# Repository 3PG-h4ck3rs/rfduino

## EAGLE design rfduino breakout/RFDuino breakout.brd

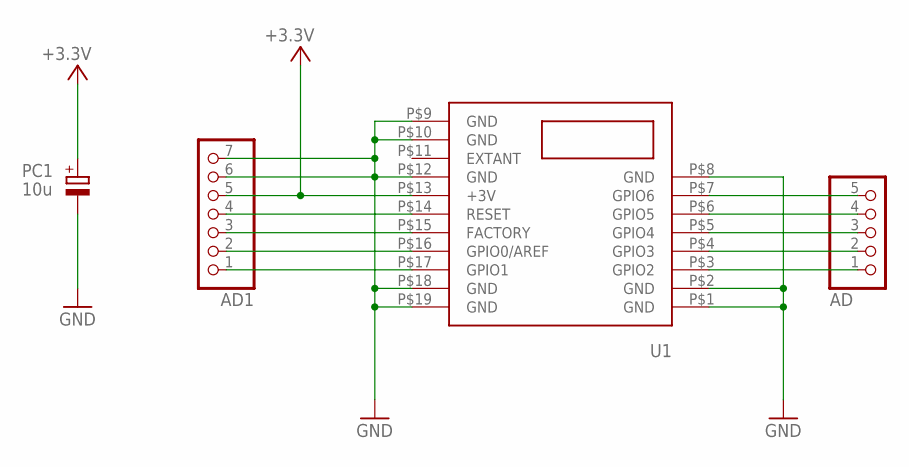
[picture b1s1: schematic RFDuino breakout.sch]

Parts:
AD: PINHD-1X5; 1X05
AD1: PINHD-1X7; 1X07
PC1: 10u; PANASONIC_D
U1: RFD22301

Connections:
3.3V: AD1.5, PC1.+, U1.P$13 (+3V)
FACTORY: AD1.3, U1.P$15 (FACTORY)
GND: AD1.6, AD1.7, PC1.-, U1.P$1 (GND), U1.P$2 (GND), U1.P$8 (GND), U1.P$9 (GND), U1.P$10 (GND), U1.P$12 (GND), U1.P$18 (GND), U1.P$19 (GND)
GPIO0: AD1.2, U1.P$16 (GPIO0/AREF)
GPIO1: AD1.1, U1.P$17 (GPIO1)
GPIO2: AD.1, U1.P$3 (GPIO2)
GPIO3: AD.2, U1.P$4 (GPIO3)
GPIO4: AD.3, U1.P$5 (GPIO4)
GPIO5: AD.4, U1.P$6 (GPIO5)
GPIO6: AD.5, U1.P$7 (GPIO6)
RESET: AD1.4, U1.P$14 (RESET)

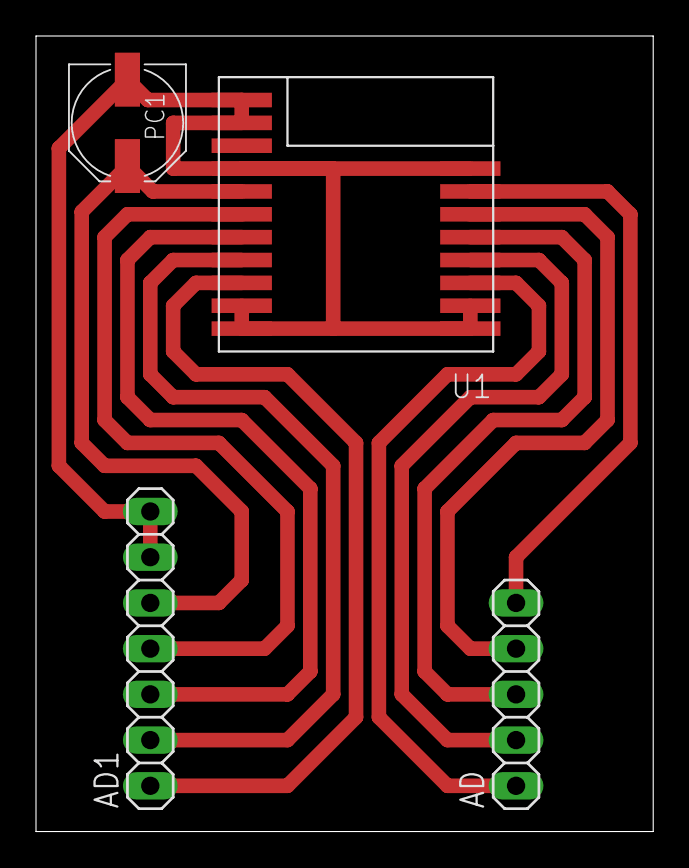
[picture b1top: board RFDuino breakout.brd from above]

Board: 2 copper layers, 34.3 x 44.2 mm, 4 parts (0 on the bottom side), 11 nets.

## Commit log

2014-10-21 sketch and breakout board
